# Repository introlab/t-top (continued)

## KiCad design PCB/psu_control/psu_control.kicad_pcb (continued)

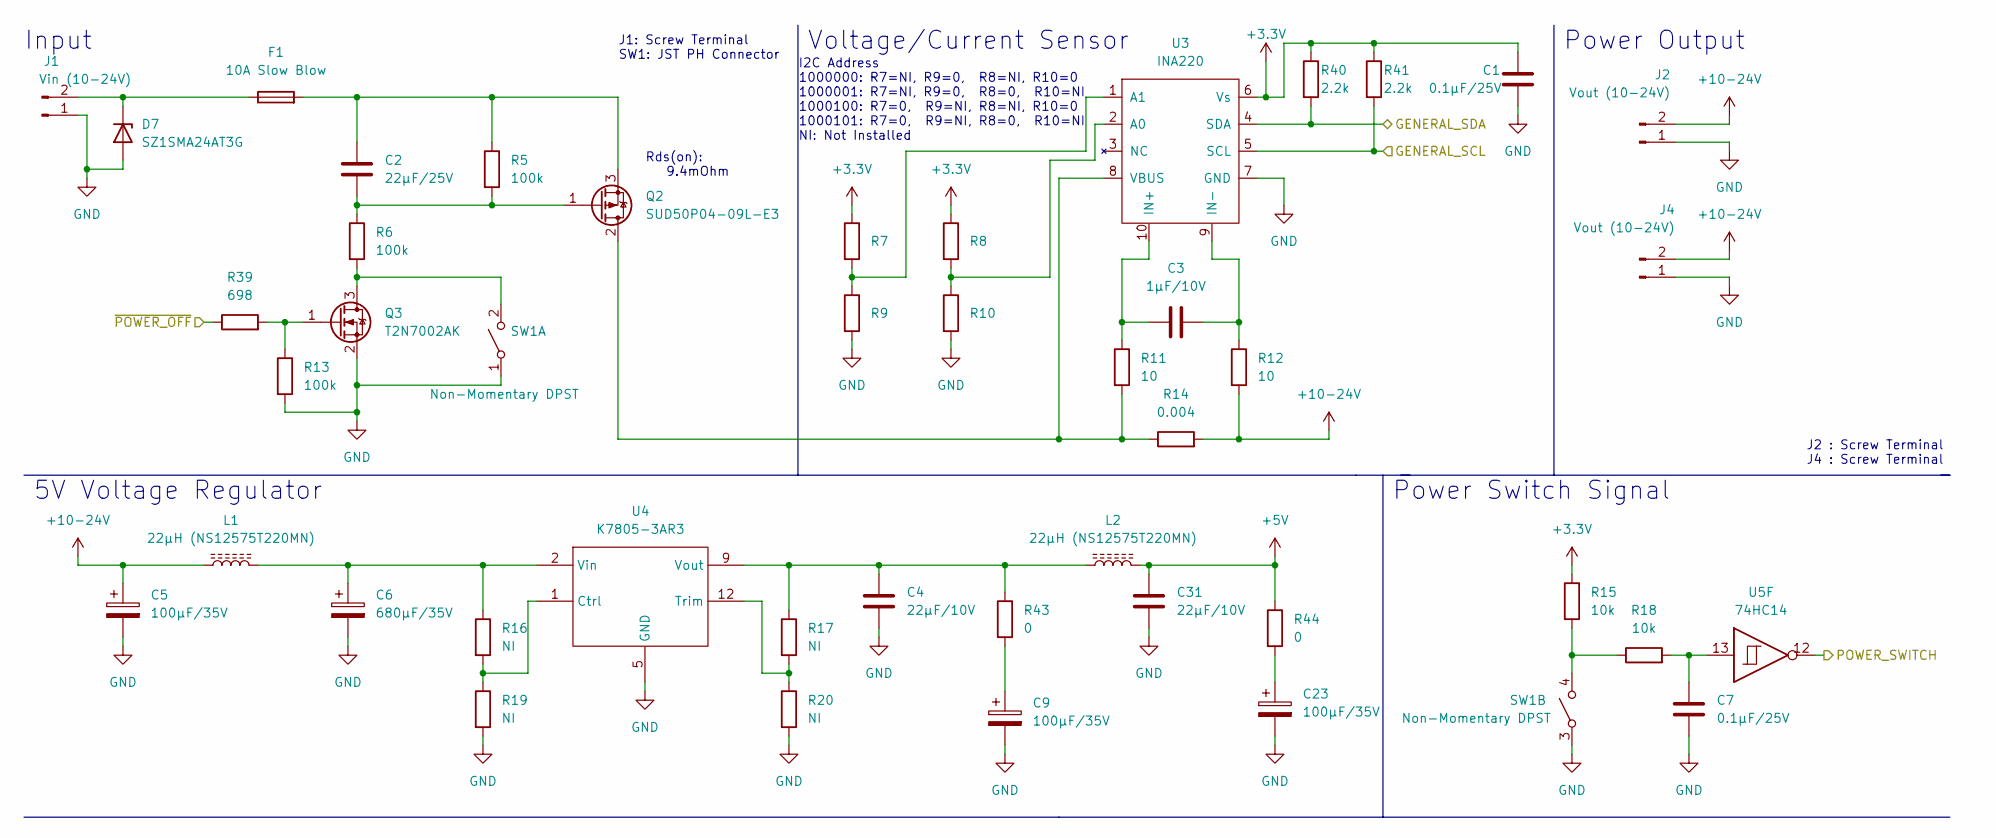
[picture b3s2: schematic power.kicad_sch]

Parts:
C1, C7: 0.1µF/25V; C_0805_2012Metric
C2: 22µF/25V; C_0805_2012Metric
C3: 1µF/10V; C_0805_2012Metric
C4, C31: 22μF/10V; C_0805_2012Metric
C5, C9, C23: 100µF/35V; CP_Radial_D6.3mm_P2.50mm
C6: 680µF/35V; CP_Radial_D10.0mm_P5.00mm
D7: SZ1SMA24AT3G; D_SMA
F1: 10A Slow Blow; M205_FUSE
J1: Vin (10-24V); OSTTA020161
J2, J4: Vout (10-24V); OSTTA020161
L1, L2: 22µH (NS12575T220MN); NS12575T220MN
Q2: SUD50P04-09L-E3; TO-252-2
Q3: T2N7002AK; SOT-23
R5, R6, R13: 100k; R_0805_2012Metric
R7, R8, R9, R10: 0; R_0805_2012Metric
R11, R12: 10; R_0805_2012Metric
R14: 0.004; R_1206_3216Metric
R15, R18: 10k; R_0805_2012Metric
R16, R17, R19, R20: NI; R_0805_2012Metric
R39: 698; R_0805_2012Metric
R40, R41: 2.2k; R_0805_2012Metric
R43, R44: 0; R_1206_3216Metric
SW1: Non-Momentary DPST; JST_PH_B4B-PH-K_1x04_P2.00mm_Vertical
U3: INA220; VSSOP-10_3x3mm_P0.5mm
U4: K7805-3AR3
U5: 74HC14; TSSOP-14_4.4x5mm_P0.65mm

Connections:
10-25V: C5.1, J2.2, J4.2, L1.1, R12.2, R14.2
+3.3V: C1.1, R7.1, R8.1, R15.1, R40.1, R41.1, U3.6 (Vs); also elsewhere on the board
+5V: C31.1, L2.2, R44.1; also elsewhere on the board
/GENERAL_SCL: R41.2, U3.5 (SCL); also elsewhere on the board
/GENERAL_SDA: R40.2, U3.4 (SDA); also elsewhere on the board
/POWER_SWITCH: U5.12; also elsewhere on the board
/~POWER_OFF: R39.1; also elsewhere on the board
GND: C1.2, C4.2, C5.2, C6.2, C7.2, C9.2, C23.2, C31.2, D7.2 (A), J1.1, J2.1, J4.1, Q3.2 (S), R9.2, R10.2, R13.2, R19.2, R20.2, SW1.1 (A), SW1.3 (A), U3.7 (GND), U4.5 (GND); also elsewhere on the board
unnamed: C2.1, F1.2, Q2.3 (S), R5.1
unnamed: C2.2, Q2.1 (G), R5.2, R6.1
unnamed: C3.1, R11.1, U3.10 (IN+)
unnamed: C3.2, R12.1, U3.9 (IN-)
unnamed: C4.1, L2.1, R17.1, R43.1, U4.9 (Vout)
unnamed: C6.1, L1.2, R16.1, U4.2 (Vin)
unnamed: C7.1, R18.2, U5.13
unnamed: C9.1, R43.2
unnamed: C23.1, R44.2
unnamed: D7.1 (K), F1.1, J1.2
unnamed: Q2.2 (D), R11.2, R14.1, U3.8 (VBUS)
unnamed: Q3.1 (G), R13.1, R39.2
unnamed: Q3.3 (D), R6.2, SW1.2 (B)
unnamed: R7.2, R9.1, U3.1 (A1)
unnamed: R8.2, R10.1, U3.2 (A0)
unnamed: R15.2, R18.1, SW1.4 (B)
unnamed: R16.2, R19.1, U4.1 (Ctrl)
unnamed: R17.2, R20.1, U4.12 (Trim)

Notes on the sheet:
Input
Power Output
Rds(on): 9.4mOhm
Power Switch Signal
J1: Screw Terminal SW1: JST PH Connector
5V Voltage Regulator
I2C Address 1000000: R7=NI, R9=0, R8=NI, R10=0 1000001: R7=NI, R9=0, R8=0, R10=NI 1000100: R7=0, R9=NI, R8=NI, R10=0 1000101: R7=0, R9=NI, R8=0, R10=NI NI: Not Installed
Voltage/Current Sensor
J2 : Screw Terminal J4 : Screw Terminal

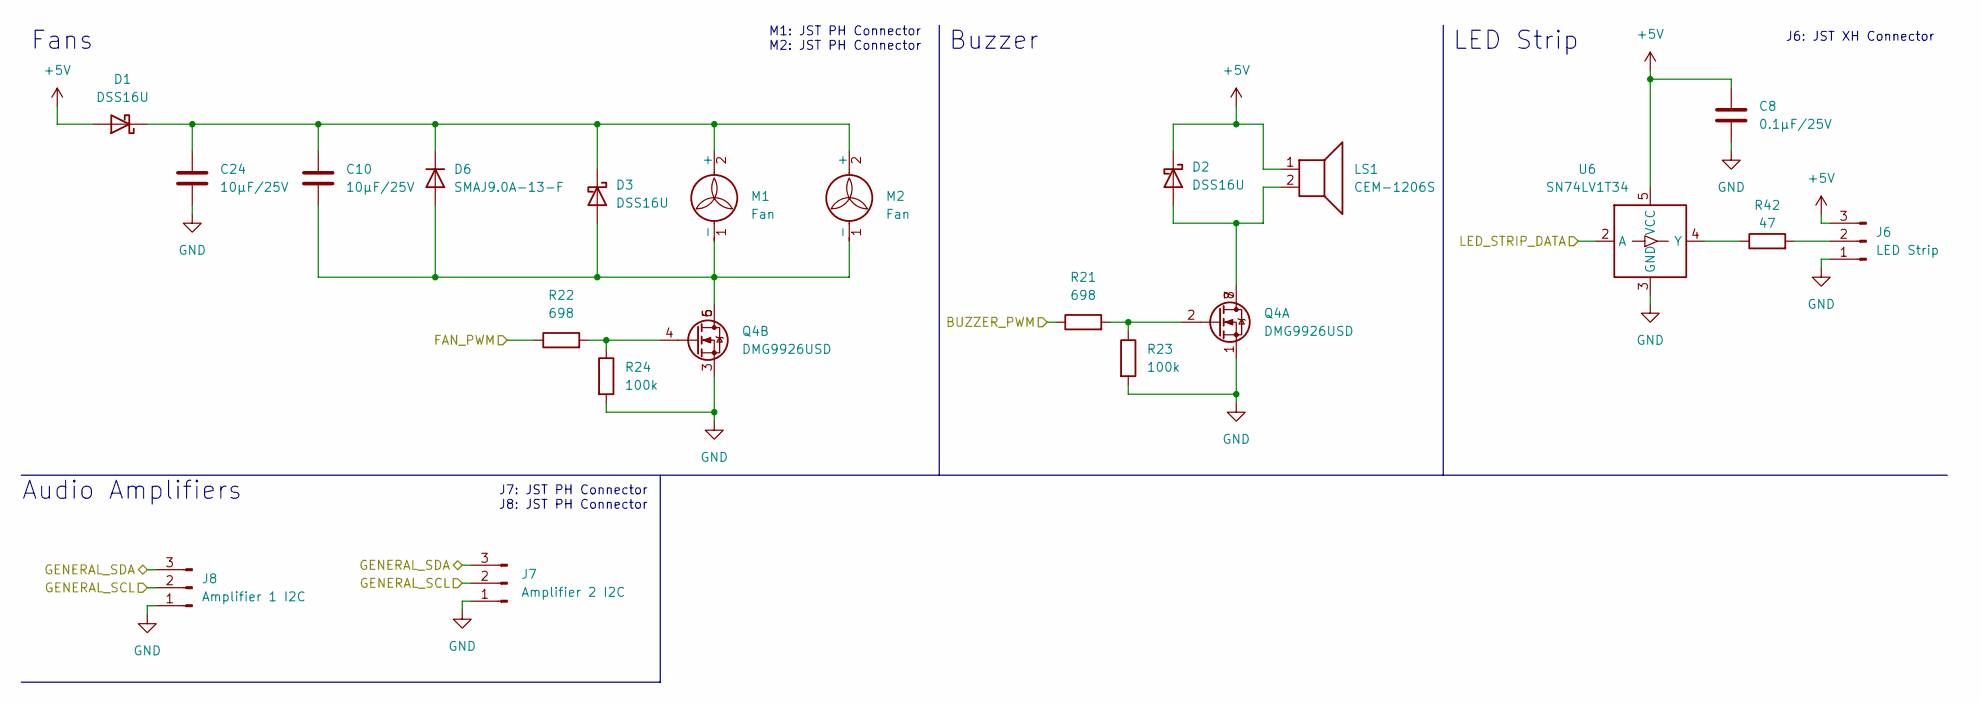
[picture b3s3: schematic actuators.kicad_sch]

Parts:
C8: 0.1µF/25V; C_0805_2012Metric
C10, C24: 10µF/25V; C_0805_2012Metric
D1, D2, D3: DSS16U; D_SOD-123F
D6: SMAJ9.0A-13-F; D_SMA
J6: LED Strip; JST_XH_B3B-XH-A_1x03_P2.50mm_Vertical
J7: Amplifier 2 I2C; JST_PH_B3B-PH-K_1x03_P2.00mm_Vertical
J8: Amplifier 1 I2C; JST_PH_B3B-PH-K_1x03_P2.00mm_Vertical
LS1: CEM-1206S; WT-1205
M1, M2: Fan; JST_PH_B2B-PH-K_1x02_P2.00mm_Vertical
Q4: DMG9926USD; SOIC-8_3.9x4.9mm_P1.27mm
R21, R22: 698; R_0805_2012Metric
R23, R24: 100k; R_0805_2012Metric
R42: 47; R_0805_2012Metric
U6: SN74LV1T34; SOT-23-5

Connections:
+5V: C8.1, D1.2 (A), D2.1 (K), J6.3, LS1.1, U6.5 (VCC); also elsewhere on the board
/Actuators/BUZZER_PWM: R21.1; also elsewhere on the board
/Actuators/FAN_PWM: R22.1; also elsewhere on the board
/Actuators/LED_STRIP_DATA: U6.2 (A); also elsewhere on the board
/GENERAL_SCL: J7.2, J8.2; also elsewhere on the board
/GENERAL_SDA: J7.3, J8.3; also elsewhere on the board
GND: C8.2, C24.2, J6.1, J7.1, J8.1, Q4.1 (S), Q4.3 (S), R23.2, R24.2, U6.3 (GND); also elsewhere on the board
unnamed: C10.1, C24.1, D1.1 (K), D3.1 (K), D6.1 (K), M1.2 (+), M2.2 (+)
unnamed: C10.2, D3.2 (A), D6.2 (A), M1.1 (-), M2.1 (-), Q4.5 (D), Q4.6 (D)
unnamed: D2.2 (A), LS1.2, Q4.7 (D), Q4.8 (D)
unnamed: J6.2, R42.2
unnamed: Q4.2 (G), R21.2, R23.1
unnamed: Q4.4 (G), R22.2, R24.1
unnamed: R42.1, U6.4 (Y)

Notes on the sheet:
Buzzer
Fans
J6: JST XH Connector
LED Strip
Audio Amplifiers
M1: JST PH Connector M2: JST PH Connector
J7: JST PH Connector J8: JST PH Connector

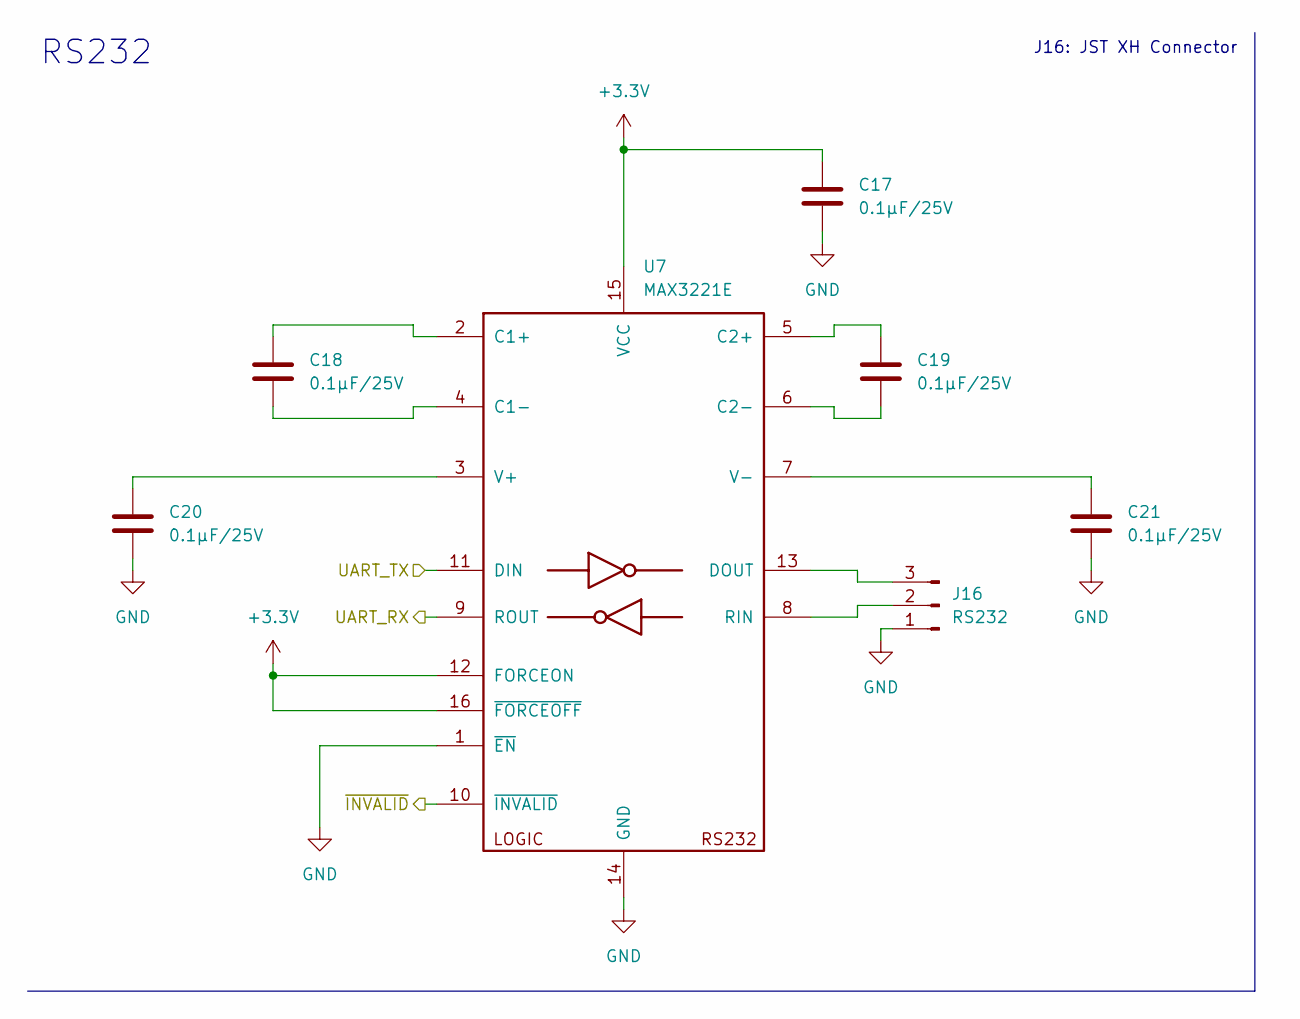
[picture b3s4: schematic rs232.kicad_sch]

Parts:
C17, C18, C19, C20, C21: 0.1µF/25V; C_0805_2012Metric
J16: RS232; JST_PH_B3B-PH-K_1x03_P2.00mm_Vertical
U7: MAX3221E; TSSOP-16_4.4x5mm_P0.65mm

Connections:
+3.3V: C17.1, U7.12 (FORCEON), U7.15 (VCC), U7.16 (~FORCEOFF); also elsewhere on the board
/RS232/UART_RX: U7.9 (ROUT); also elsewhere on the board
/RS232/UART_TX: U7.11 (DIN); also elsewhere on the board
/~RS232_INVALID: U7.10 (~INVALID); also elsewhere on the board
GND: C17.2, C20.2, C21.2, J16.1, U7.1 (~EN), U7.14 (GND); also elsewhere on the board
unnamed: C18.1, U7.2 (C1+)
unnamed: C18.2, U7.4 (C1-)
unnamed: C19.1, U7.5 (C2+)
unnamed: C19.2, U7.6 (C2-)
unnamed: C20.1, U7.3 (V+)
unnamed: C21.1, U7.7 (V-)
unnamed: J16.2, U7.8 (RIN)
unnamed: J16.3, U7.13 (DOUT)

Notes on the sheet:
J16: JST XH Connector
RS232

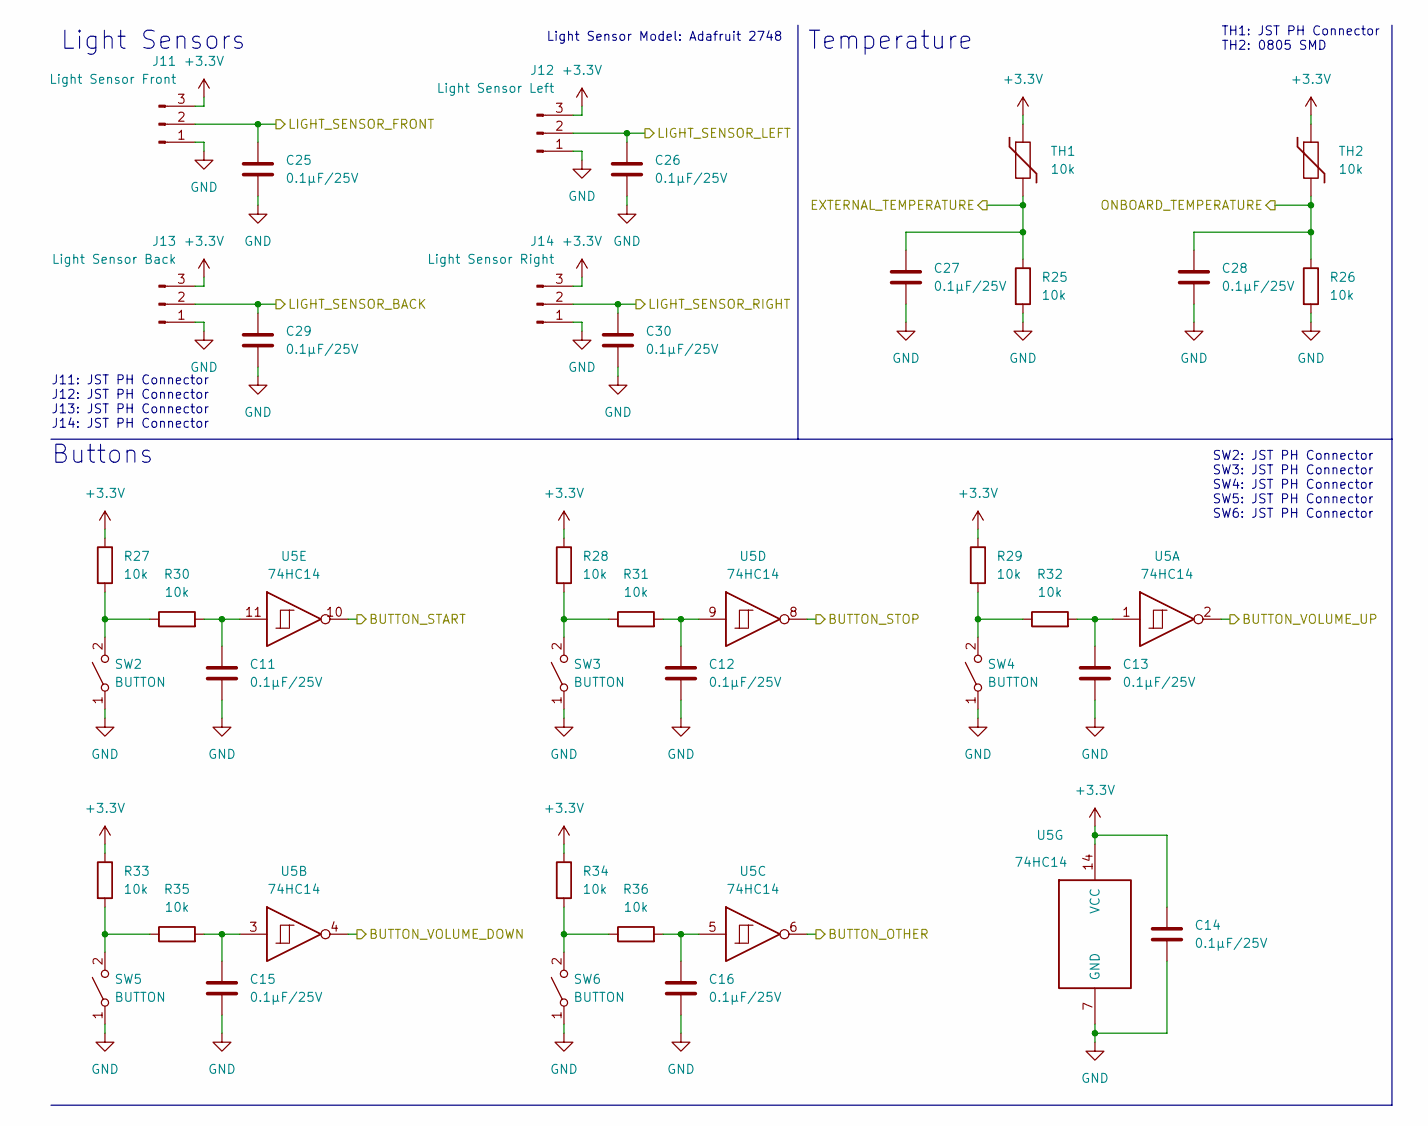
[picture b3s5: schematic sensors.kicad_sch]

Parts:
C11, C12, C13, C14, C15, C16, C25, C26, C27, C28, C29, C30: 0.1µF/25V; C_0805_2012Metric
J11: Light Sensor Front; JST_PH_B3B-PH-K_1x03_P2.00mm_Vertical
J12: Light Sensor Left; JST_PH_B3B-PH-K_1x03_P2.00mm_Vertical
J13: Light Sensor Back; JST_PH_B3B-PH-K_1x03_P2.00mm_Vertical
J14: Light Sensor Right; JST_PH_B3B-PH-K_1x03_P2.00mm_Vertical
R25, R26, R27, R28, R29, R30, R31, R32, R33, R34, R35, R36: 10k; R_0805_2012Metric
SW2, SW3, SW4, SW5, SW6: BUTTON; JST_PH_B2B-PH-K_1x02_P2.00mm_Vertical
TH1: 10k; JST_PH_B2B-PH-K_1x02_P2.00mm_Vertical
TH2: 10k; R_0805_2012Metric
U5: 74HC14; TSSOP-14_4.4x5mm_P0.65mm

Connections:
+3.3V: C14.1, J11.3, J12.3, J13.3, J14.3, R27.1, R28.1, R29.1, R33.1, R34.1, TH1.1, TH2.1, U5.14 (VCC); also elsewhere on the board
/BUTTON_OTHER: U5.6; also elsewhere on the board
/BUTTON_START: U5.10; also elsewhere on the board
/BUTTON_STOP: U5.8; also elsewhere on the board
/BUTTON_VOLUME_DOWN: U5.4; also elsewhere on the board
/BUTTON_VOLUME_UP: U5.2; also elsewhere on the board
/LIGHT_SENSOR_BACK: C29.1, J13.2; also elsewhere on the board
/LIGHT_SENSOR_RIGHT: C30.1, J14.2; also elsewhere on the board
/Sensors/EXTERNAL_TEMPERATURE: C27.1, R25.1, TH1.2; also elsewhere on the board
/Sensors/LIGHT_SENSOR_FRONT: C25.1, J11.2; also elsewhere on the board
/Sensors/LIGHT_SENSOR_LEFT: C26.1, J12.2; also elsewhere on the board
/Sensors/ONBOARD_TEMPERATURE: C28.1, R26.1, TH2.2; also elsewhere on the board
GND: C11.2, C12.2, C13.2, C14.2, C15.2, C16.2, C25.2, C26.2, C27.2, C28.2, C29.2, C30.2, J11.1, J12.1, J13.1, J14.1, R25.2, R26.2, SW2.1 (A), SW3.1 (A), SW4.1 (A), SW5.1 (A), SW6.1 (A), U5.7 (GND); also elsewhere on the board
unnamed: C11.1, R30.2, U5.11
unnamed: C12.1, R31.2, U5.9
unnamed: C13.1, R32.2, U5.1
unnamed: C15.1, R35.2, U5.3
unnamed: C16.1, R36.2, U5.5
unnamed: R27.2, R30.1, SW2.2 (B)
unnamed: R28.2, R31.1, SW3.2 (B)
unnamed: R29.2, R32.1, SW4.2 (B)
unnamed: R33.2, R35.1, SW5.2 (B)
unnamed: R34.2, R36.1, SW6.2 (B)

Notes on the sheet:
Buttons
SW2: JST PH Connector SW3: JST PH Connector SW4: JST PH Connector SW5: JST PH Connector SW6: JST PH Connector
TH1: JST PH Connector TH2: 0805 SMD
Light Sensors
Temperature
J11: JST PH Connector J12: JST PH Connector J13: JST PH Connector J14: JST PH Connector
Light Sensor Model: Adafruit 2748

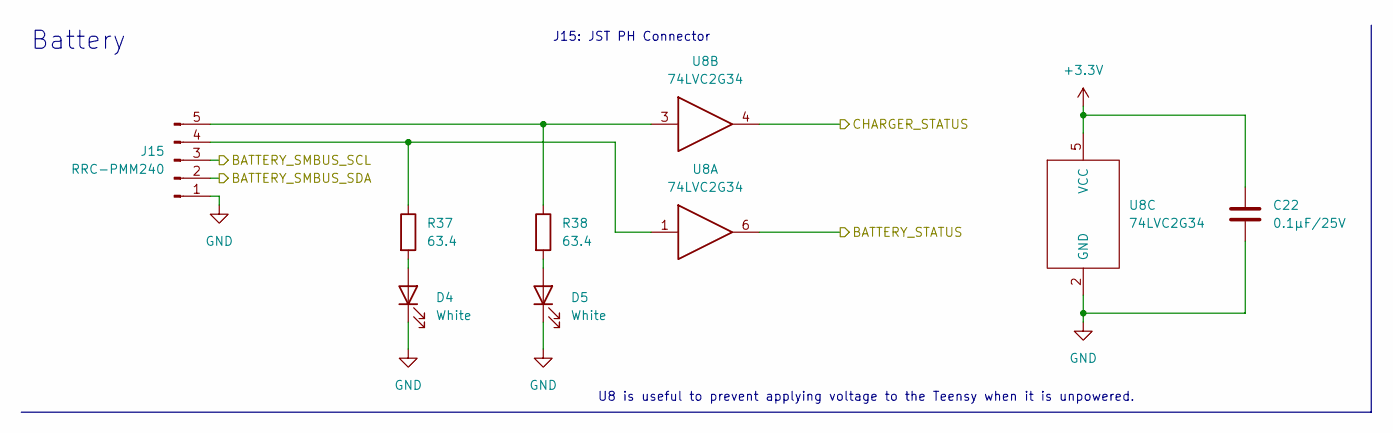
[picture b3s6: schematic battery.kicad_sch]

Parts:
C22: 0.1µF/25V; C_0805_2012Metric
D4, D5: White; JST_PH_B2B-PH-K_1x02_P2.00mm_Vertical
J15: RRC-PMM240; JST_PH_B5B-PH-K_1x05_P2.00mm_Vertical
R37, R38: 63.4; R_0805_2012Metric
U8: 74LVC2G34; TSOP-6_1.65x3.05mm_P0.95mm

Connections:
+3.3V: C22.1, U8.5 (VCC); also elsewhere on the board
/Battery/BATTERY_SMBUS_SCL: J15.3; also elsewhere on the board
/Battery/BATTERY_SMBUS_SDA: J15.2; also elsewhere on the board
/Battery/BATTERY_STATUS: U8.6; also elsewhere on the board
/Battery/CHARGER_STATUS: U8.4; also elsewhere on the board
GND: C22.2, D4.1 (K), D5.1 (K), J15.1, U8.2 (GND); also elsewhere on the board
unnamed: D4.2 (A), R37.2
unnamed: D5.2 (A), R38.2
unnamed: J15.4, R37.1, U8.1
unnamed: J15.5, R38.1, U8.3

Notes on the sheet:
Battery
U8 is useful to prevent applying voltage to the Teensy when it is unpowered.
J15: JST PH Connector

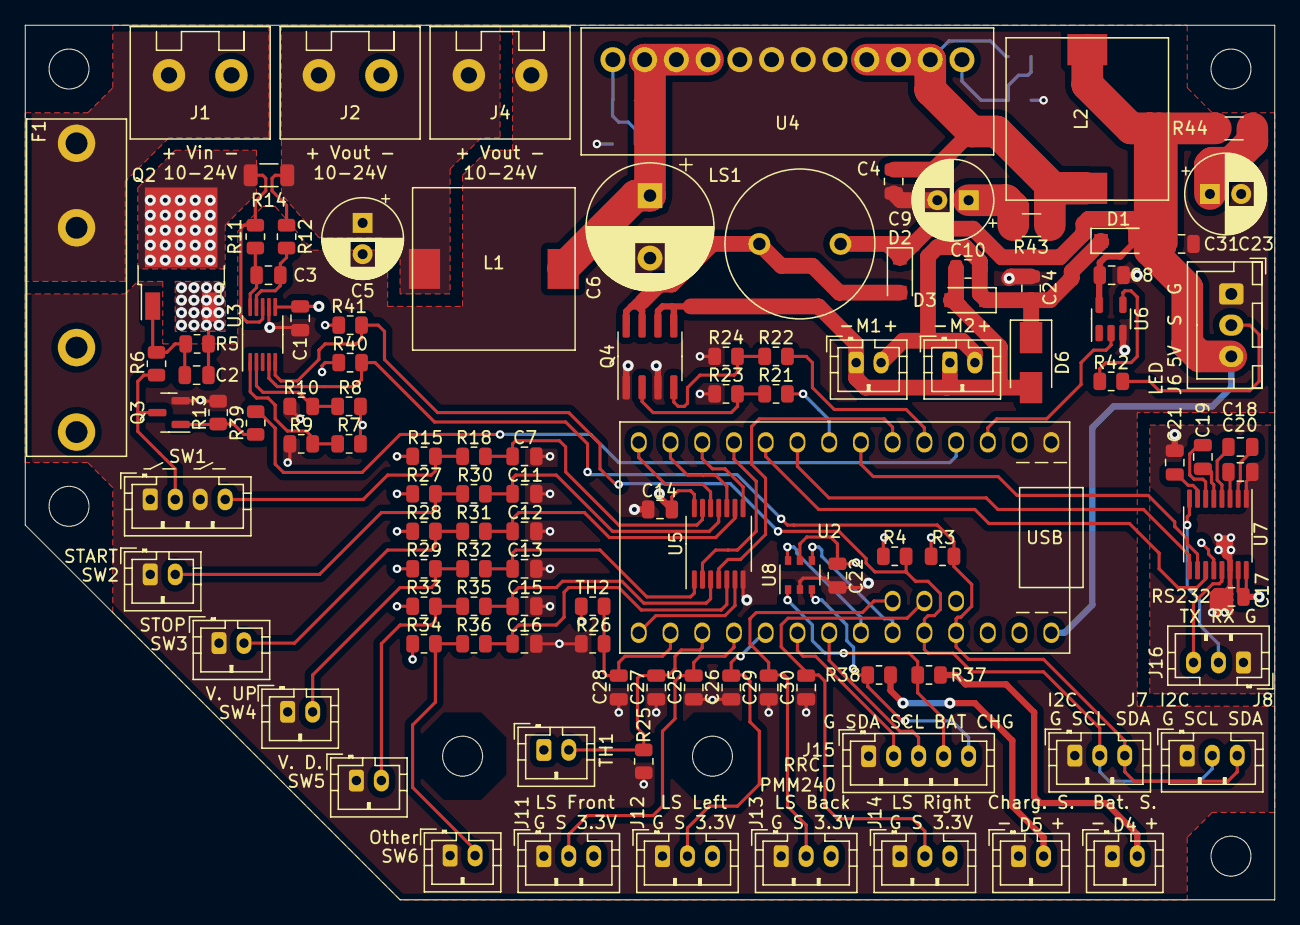
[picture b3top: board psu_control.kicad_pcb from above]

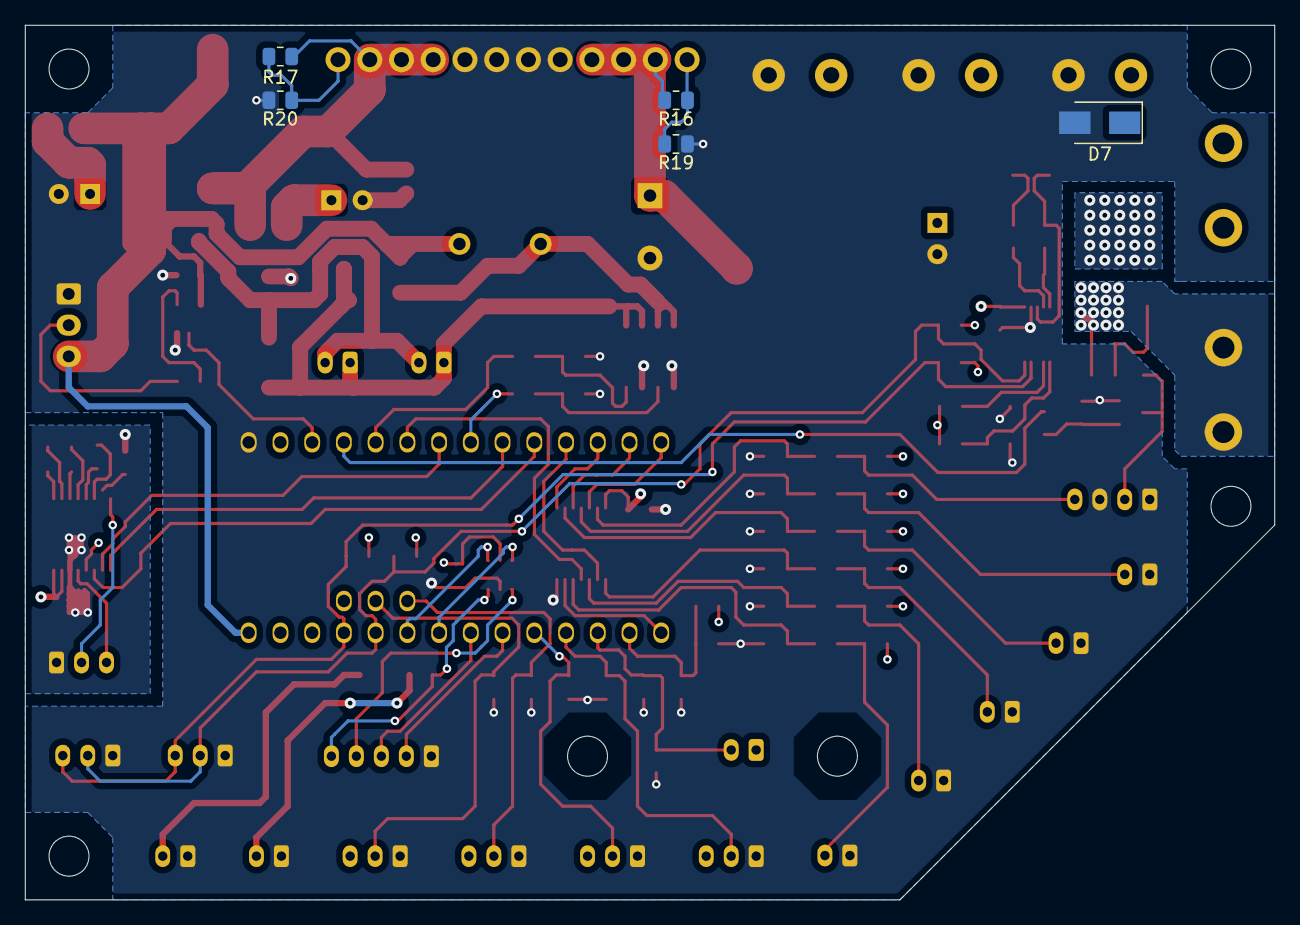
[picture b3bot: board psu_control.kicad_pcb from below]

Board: 4 copper layers, 100.0 x 70.0 mm, 116 parts (5 on the bottom side), 76 nets.

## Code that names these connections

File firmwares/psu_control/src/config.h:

#ifndef PSU_CONTROL_CONFIG_H
#define PSU_CONTROL_CONFIG_H

#include <cstdint>
#include <cstddef>

// Firmware configuration
#define FIRMWARE_MODE_SETUP_BATTERY_CHARGER 1
#define FIRMWARE_MODE_NORMAL                2
#define FIRMWARE_MODE_PCB_TEST              3
#define FIRMWARE_MODE_COMMUNICATION_TEST    4
#define FIRMWARE_MODE                       FIRMWARE_MODE_NORMAL

// Device configuration
#define DEBUG_SERIAL Serial
constexpr long DEBUG_SERIAL_BAUD_RATE = 250000;

constexpr uint32_t WIRE_CLOCK = 100000;

constexpr uint32_t PWM_RESOLUTION = 12;
constexpr float PWM_MAX_VALUE = 4095.f;

constexpr uint32_t ADC_RESOLUTION = 12;
constexpr float ADC_MAX_VALUE = 4095.f;

constexpr uint8_t POWER_OFF_PIN = 2;
constexpr uint8_t POWER_SWITCH_PIN = 12;
constexpr uint32_t SHUTDOWN_REQUEST_TIMEOUT_MS = 120000;
constexpr float SHUTDOWN_COMPLETED_FOR_COMPUTER_AND_DYNAMIXELS_POWER_THRESHOLD_W = 7.5f;

#define BATTERY_WIRE Wire
constexpr uint8_t BATTERY_STATUS_PIN = 20;
constexpr uint8_t CHARGER_STATUS_PIN = 21;
constexpr float BATTERY_CHARGER_CHARGE_CURRENT_LIMIT = 1.f;
constexpr float BATTERY_CHARGER_INPUT_CURRENT_LIMIT = 9.47f;

constexpr uint8_t LED_STRIP_PIN = 1;
constexpr size_t STATE_OF_CHARGE_LED_COUNT = 5;
constexpr size_t VOLUME_LED_COUNT = 5;
constexpr size_t BASE_LED_COUNT = 28;
constexpr size_t LED_COUNT = STATE_OF_CHARGE_LED_COUNT + VOLUME_LED_COUNT + BASE_LED_COUNT;
constexpr uint8_t LED_STRIP_MINIMUM_BRIGHTNESS = 64;
constexpr uint8_t LED_STRIP_MAXIMUM_BRIGHTNESS = 128;

constexpr uint8_t FAN_PIN = 3;
constexpr float FAN_PWM_FREQUENCY = 46875;
constexpr float FAN_HYSTERESIS = 1;
constexpr float FAN_TEMPERATURE_STEP_1 = 40;
constexpr float FAN_TEMPERATURE_STEP_2 = 60;

constexpr uint8_t BUZZER_PIN = 6;
constexpr float BUZZER_PWM_FREQUENCY = 2400;
constexpr uint32_t BUZZER_ON_OFF_INTERVAL_US = 1000000;
constexpr float BUZZER_STATE_OF_CHARGE_LIMIT = 5;

#define AUDIO_POWER_AMPLIFIER_WIRE Wire1
constexpr size_t AUDIO_POWER_AMPLIFIER_COUNT = 2;
constexpr uint8_t AUDIO_POWER_AMPLIFIER_I2C_ADDRESSES[AUDIO_POWER_AMPLIFIER_COUNT] = {0x4a, 0x4b};
constexpr uint8_t AUDIO_POWER_AMPLIFIER_DEFAULT_VOLUME = 24;
constexpr uint8_t AUDIO_POWER_AMPLIFIER_BATTERY_MAXIMUM_VOLUME = 45;
constexpr uint8_t AUDIO_POWER_AMPLIFIER_MAXIMUM_VOLUME = 63;

#define CURRENT_VOLTAGE_SENSOR_WIRE Wire1
constexpr uint8_t CURRENT_VOLTAGE_SENSOR_ADDRESS = 0x40;
constexpr float CURRENT_VOLTAGE_SENSOR_SHUNT_RESISTOR = 0.004f;
constexpr uint8_t CURRENT_VOLTAGE_SENSOR_MAX_CURRENT = 10;

constexpr uint8_t ONBOARD_TEMPERATURE_PIN = 14;
constexpr float ONBOARD_TEMPERATURE_NTC_R = 10000;  // @ 25°C
constexpr float ONBOARD_TEMPERATURE_NTC_BETA = 3940;
constexpr float ONBOARD_TEMPERATURE_R = 10000;
constexpr uint8_t EXTERNAL_TEMPERATURE_PIN = 15;
constexpr float EXTERNAL_TEMPERATURE_NTC_R = 10000;  // @ 25°C
constexpr float EXTERNAL_TEMPERATURE_NTC_BETA = 3936;
constexpr float EXTERNAL_TEMPERATURE_R = 10000;

constexpr uint8_t FRONT_LIGHT_SENSOR_PIN = 16;
constexpr uint8_t BACK_LIGHT_SENSOR_PIN = 25;
constexpr uint8_t LEFT_LIGHT_SENSOR_PIN = 17;
constexpr uint8_t RIGHT_LIGHT_SENSOR_PIN = 24;
constexpr float LIGHT_SENSOR_MINIMUM_VALUE = ADC_MAX_VALUE * 0.0f;
constexpr float LIGHT_SENSOR_MAXIMUM_VALUE = ADC_MAX_VALUE * 0.03f;

constexpr uint8_t START_BUTTON_PIN = 11;
constexpr uint8_t STOP_BUTTON_PIN = 10;
constexpr uint8_t VOLUME_UP_BUTTON_PIN = 9;
constexpr uint8_t VOLUME_DOWN_BUTTON_PIN = 4;
constexpr uint32_t VOLUME_BUTTON_INTERVAL_MS = 250;

// Communication configuration
#define COMMUNICATION_SERIAL Serial3
constexpr uint8_t COMMUNICATION_RS232_INVALID = 5;
constexpr long COMMUNICATION_SERIAL_BAUD_RATE = 250000;
constexpr uint32_t COMMUNICATION_ACKNOWLEDGMENT_TIMEOUT_MS = 100;
constexpr uint32_t COMMUNICATION_MAXIMUM_TRIAL_COUNT = 5;

// Timing configuration
constexpr uint32_t ERROR_DELAY_MS = 1000;
constexpr uint32_t STATUS_TICKER_INTERVAL_MS = 250;
constexpr uint32_t BUTTON_TICKER_INTERVAL_MS = 100;
constexpr uint32_t SHUTDOWN_PENDING_DELAY_MS = 1000;

#endif

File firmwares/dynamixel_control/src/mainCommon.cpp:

#include "mainCommon.h"

Icm40627 imu(Wire, IMU_INT1_PIN, IMU_INT2_PIN, IMU_ADDRESS);
Dynamixel2Arduino dynamixel(DYNAMIXEL_SERIAL, DYNAMIXEL_DIR_PIN);

void setupDebugSerial()
{
    DEBUG_SERIAL.begin(DEBUG_SERIAL_BAUD_RATE);
}

void setupWire()
{
    DEBUG_SERIAL.println("Setup Wire - Start");
    Wire.setClock(WIRE_CLOCK);
    Wire.begin();
    DEBUG_SERIAL.println("Setup Wire - End");
}

void setupImu()
{
    DEBUG_SERIAL.println("Setup Imu - Start");
    if (!imu.begin(IMU_ACCELEROMETER_RANGE, IMU_GYROSCOPE_RANGE, IMU_ODR, IMU_ANTI_ALIAS_FILTER_BANDWIDTH))
    {
        CRITICAL_ERROR("Setup Imu - failure");
    }
    DEBUG_SERIAL.println("Setup Imu - End");
}

void setupImu(void (*dataReadyInterrupt)())
{
    DEBUG_SERIAL.println("Setup Imu - Start");
    if (!imu.begin(IMU_ACCELEROMETER_RANGE, IMU_GYROSCOPE_RANGE, IMU_ODR, IMU_ANTI_ALIAS_FILTER_BANDWIDTH, dataReadyInterrupt))
    {
        CRITICAL_ERROR("Setup Imu - failure");
    }
    DEBUG_SERIAL.println("Setup Imu - End");
}

void setupDynamixel()
{
    DEBUG_SERIAL.println("Setup Dynamixel - Start");

    pinMode(DYNAMIXEL_ENABLE_PIN, OUTPUT);
    digitalWrite(DYNAMIXEL_ENABLE_PIN, true);

    dynamixel.begin(DYNAMIXEL_BAUD_RATE);
    delay(SETUP_DYNAMIXEL_DELAY_MS);

    DEBUG_SERIAL.println("Setup Dynamixel - End");
}

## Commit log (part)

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2023-11-18 Update tab_leds.png in control_panel.
2023-11-20 Improve robot name detection.
2023-11-20 Fix createRobotNameDetectorWithLedStatusDesireStrategy
2023-11-20 Add prebuffering to whisper_speech_to_text_node.py.
2023-11-20 Fix whisper_speech_to_text_node activation. Fix robot_name_detector status disabling.
2023-11-20 Reset the fast sound rms filter to prevent triggering at the activation of the node.
2023-11-20 Fix robot_name_detector.
2023-11-20 Fix connect4.launch
2023-11-20 Fix robot_name_detector inference_type.
2023-11-22 Added slow_origin_head and thinking gestures
2023-11-26 Add the node to analyze the performance of YOLO models.
2023-11-27 Update nvpmodel.
2023-12-04 Update SHUTDOWN_COMPLETED_FOR_COMPUTER_AND_DYNAMIXELS_POWER_THRESHOLD_W.
2023-12-05 Add a watchdog node for the wide-angle camera.
2023-12-05 Add arbitration for the head pose and torso orientation.
2023-12-06 Fix sound_following_node.py
2023-12-06 Fix face_following_nodes
2023-12-06 Fix too_near_reaction.launch
2023-12-06 Reset the offset of too_near_reaction on disabling.
2023-12-06 Add the video analysis object in the pose classification message.
2023-12-06 Rename too near reaction to too close reaction.
2023-12-07 Complete yolo_performance.
2023-12-10 Ubc demo (#83)
    * Disable semantic segmentation.
    * Add pose classification.
    * Remove prints.
    * Increased timeout to 20 sec and use google cloud url. Use wide angle camera for pose classification.
    * Decrease presence threshold
    * Cache size is now 1000
2023-12-10 Use a uuid for the image filename.
2023-12-12 5s watchdog
2023-12-19 Add the LED animation when a participant win a game.
2023-12-19 Update opentera-webrtc
2024-01-10 Use web socket to get the game feedback.
2024-01-10 Yolo detection results (#84)
    * Add the node to analyze the performance of YOLO models.
    * Complete yolo_performance.
    * Add the scripts to the CMakeLists.txt
    * Use a uuid for the image filename.
2024-01-11 Add face orientation replication draft.
2024-01-11 Add topic args to the data channel launch file.
2024-01-11 Add webrtc face orientation.
2024-01-15 Update HBBA Lite
2024-01-15 Update hbba_lite
2024-01-16 Update opentera-webrtc-ros.
2024-01-16 Adjust face orientation replication parameters.
2024-01-17 Add head_roll_image_rotation_node.py draft.
2024-01-17 Fix rotation direction.
2024-01-19 Set the stamp and seq of the output msg.
2024-01-26 Update papers in README.md.
2024-02-20 fix delay before talk done
2024-02-20 Fix talk done delay. Fix when cache size is zero. Delete cache files when needed.
2024-03-19 Add yolo model arguments to the bringup.launch. Fix the dnn_utils readme. Add class AP for multiclass audio classification.
2024-03-20 Fix bringup.launch
2024-04-03 Removed ROS print
2024-04-05 Added stats to transcript
2024-04-05 Fixing google processing time and sample count
2024-04-08 Try calling API for stats
2024-04-08 GitHub stats (#91)
    * Try calling API for stats
    * Try calling API for stats
    * Try calling API for stats
    * Try calling API for stats
    * Try calling API for stats
    * Update scheduled-stats.yml
2024-04-09 Update README.md papers
2024-04-12 Adding processing time to video analysis.
2024-04-12 Adding stats to talk node
2024-04-15 Moved stats into a function
2024-04-15 Fix launch files that use video_analyzer.launch directly.
2024-04-15 Use the GPU for the face cropper.
2024-04-15 Speech stats (#92)
    * Added stats to transcript
    * Fixing google processing time and sample count
    * Updated time, looks more than the response time than the processing time since the last final sentence
    * Adding processing time to analysis message
    * Adding processing time to video analysis.
    * Adding stats to talk node
2024-04-15 Fix launch files (#93)
    * Fix launch files that use video_analyzer.launch directly.
    * Use the best network for face cropping.
    * Use the GPU for the face cropper.
    * Updated opentera-webrtc-ros
    ---------
2024-04-29 Make thresholds global for video_analyzer
2024-04-29 Updated hbba_lite to fix semaphore implementation. Now using C++ 17
2024-04-29 Adding whisper model
2024-04-29 Build the user interface at build time.
2024-04-29 Reduce the sleep duration
2024-05-03 Add a way to evaluate the descriptor yolo v7 descriptor.
2024-05-08 Adding delays when launching nodes.
2024-05-08 Fix delays (#98)
    * Build the user interface at build time.
    * Reduce the sleep duration
    * Adding delays when launching nodes.
    * add more delays
    ---------
2024-05-09 Working on ARM
2024-05-09 Fix version for ARM
2024-05-13 Update descriptor yolo v7 weights.
2024-05-14 Realsense respawn (#103)
    * Build the user interface at build time.
    * Reduce the sleep duration
    * Updated launch file to set respawn to true for realsense
    ---------
2024-05-16 Added missing delays and thresholds
2024-05-16 Building ros2 realsense node with cuda, WIP
2024-05-17 launching realsense and bridge
2024-05-28 Evaluate descriptor yolo (#102)
    * Add a way to evaluate the descriptor yolo v7 descriptor.
    * Update descriptor yolo v7 weights.
2024-05-28 Add ros2 submodules.
2024-05-28 Ignore system projects.
2024-05-28 Add dnn_utils
2024-05-28 Add daemon_ros_client
2024-05-28 Add video_analyzer
2024-05-28 Add robot_name_detector.
2024-05-28 Add speech_to_text
2024-05-30 Add t_top without launch. Refatoring.
2024-05-30 Add dance.
2024-05-30 Add gesture.
2024-05-30 Add led_emotions
2024-05-30 Add piper_ros
2024-05-30 Add sound_player
2024-05-30 Add talk
2024-05-30 Add t-top_hbba_lite
2024-05-31 Add ego_noise_reduction
2024-06-01 Fix DaemonApp.cpp. Add person_identification.
2024-06-01 Add sound_object_person_following
2024-06-01 Add yolo_performance.
2024-06-01 Add control_panel
2024-06-01 Add smart_speaker
2024-06-03 Update .gitmodules
    use https instead of git.
2024-06-03 Almost compiling RTAB-Map
2024-06-03 Changed to humble ros2 distribution
2024-06-03 Complete video_recorder_node.py
2024-06-04 Add watchdog.
2024-06-04 Format
2024-06-05 Building with rtabmap
2024-06-05 Building ok
2024-06-05 Move behavior msg to behavior_msg.
2024-06-06 updated docker build
2024-06-06 Fix for audio_utils_msg and humble.
2024-06-06 add install script
2024-06-06 Update test_video_analyzer_3d_node.launch.xml.
2024-06-07 ongoing fix for launch files
2024-06-10 set number of proc properly
2024-06-10 Fixed ROS_ROOT prefix
2024-06-10 fixed xml
2024-06-10 Fixed XML launch files
2024-06-10 fixed format parameter
2024-06-18 Fix rclpy.shutdown().
2024-06-18 Fixed shutdown, need to fix camera calibration, talk
2024-06-19 Launching works. Fixed shutdown. Fix deadlocks.
2024-06-20 Fix SQLiteCpp
2024-06-20 Fix ego_noise_reduction. Fix video_analyzer vizualisation nodes. Fix yolo_performance.
2024-06-20 Fix home_logger.
2024-06-20 Add first draft of jetson_configuration.sh for ROS2.
2024-06-21 Better dependencies export for hbba_lite and t_top_hbba_lite, simplifies CMake in demos
2024-06-21 Migrate teleoperation behavior
2024-06-22 Fix build for CMake 3.22.1
2024-06-28 Fixed compilation with hbba and odas_ros
2024-06-28 Updated odas_ros
2024-07-03 Fix delays and ifs
2024-07-03 updated gui
2024-07-03 Fix WiFi network name in robot_status
2024-07-05 Connect4 cpp migration
2024-07-05 Test face orientation working, fix launch files
2024-07-05 Added opentera-webrtc-ros
2024-07-05 Add missing ros2 packages.
2024-07-06 Update odas_ros and hbba_lite.
2024-07-12 Fix roll_angle_rad initialization
2024-07-12 Added build flags, Release
2024-07-12 Add information about ROS_DOMAIN_ID
2024-07-17 Improve audio_analyzer_node.py descriptors.
2024-07-26 Set all audio queue size to 1.
2024-11-05 Fix jetson_configuration.sh
2024-11-05 Update 13_CALIBRATION.md
    Create calib path.
2024-11-05 Update ros2_humble_install.sh
    Fix build.
2025-01-09 Fix warnings
2025-01-13 Fix warnings in submodules
2025-01-22 Fix duplicate tf, npm no longer clear terminal
2025-01-22 Fix install script for t-top v4 for ROS2, jetson orin and jetpack 5.1.4
2025-02-17 Adding ChatDesire and ChatStrategy, WIP.
2025-02-17 Demo enabling ChatStrategy working. WIP.
2025-02-19 Working chat with ollama
2025-02-20 Fix warnings (#108)
    * Fix warnings
    * Fix warnings in submodules
    * Hide npm warnings if the user_interface build is a success
    * Fix duplicate tf, npm no longer clear terminal
    * Fix install script for t-top v4 for ROS2, jetson orin and jetpack 5.1.4
    * Update submodules
2025-02-26 Updated to ros2 branch
2025-02-28 Fix websocket url in diner game, code improvements
2025-03-03 Working simple function calls
2025-03-06 Handle second next_configuration and stop event
2025-03-13 Update README.md
    Fix mailto
2025-03-13 Add files via upload
    Removed alpha.
2025-03-31 Starting work on getting started documentation
2025-04-01 Added debug configuration
2025-04-01 Starting separation into configuration files
2025-04-01 Added diner scenario handling (#109)
    * Added diner scenario handling
    * Fix websocket url in diner game, code improvements
    * Fix websocket url in diner game, code improvements
    * Fix websocket url in diner game, code improvements
    * Handle second next_configuration and stop event
2025-04-10 Getting started doc (#111)
    * Starting work on getting started documentation
    * Added control panel launch
    * Added debug configuration
    * Fixed documentation
2025-04-15 Calling external services, WIP
2025-04-16 Callbacks blocking after calling service, why ?
2025-04-16 Trying another thread, same result, not receiving subscriber message
2025-04-23 Working version to raise or lower volume
2025-04-23 Cleanup
2025-04-25 Updated documentation
2025-04-30 Fix path to file to source in integrated terminal profile
2025-04-30 Address remaining pull request comments.
2025-04-30 Add robot Wifi IP address to system tray to make it easier to check (#114)
2025-04-30 Fix path to file to source in integrated terminal profile (#113)
2025-05-01 Fix openai api for openai > 1.0.0
2025-05-09 Fix Chatbot synchronization
2025-05-12 Added new filter for chat behavior translation subscriber, republishing transcript from strategy.
2025-05-13 fixed documentation and filter activation order.
2025-05-13 fixed documentation.
2025-05-14 add perception conversation revive
2025-05-16 add weather request api
2025-05-21 add weather function call
2025-05-30 change meteo node name in launch
2025-06-03 PR modifications
2025-06-04 Added weather data for current weather
2025-06-04 Removed time from msg and added classes.json
2025-06-06 function call tools librairy
2025-06-10 Add get_activity function
2025-06-10 install and export chattools librairy
2025-06-12 Add save history capabilities + PR adjustment
2025-06-12 adjust launch file + save condition
2025-06-12 modify path
2025-06-13 meteo days index update
2025-06-16 remove chat
2025-06-18 Chat_node history save update msg + path
2025-06-27 split process response
2025-07-01 statemachine commit 1
2025-07-14 clean from stateMachine
2025-07-14 remove chat revive logic
2025-07-14 Remove Revive from ContextInput
2025-07-15 clean current object from strategy
2025-07-17 Remove old weather api
2025-07-23 tool_call adjustment
2025-07-25 update hint and plural
2025-07-25 plural fix
2025-09-05 Update Chatbot (#121)
    * skeleton
    * Adding ChatDesire and ChatStrategy, WIP.
    * Base chatbot demo
    * Demo enabling ChatStrategy working. WIP.
    * Working chat with ollama
    * Working chatbot
2025-10-06 fix save path to avoid problems with user names, make sure file is saved with proper path
2026-01-11 WIP: add compatibility with ROS2 version of TOPO
2026-02-03 Deprecated parameters for gpt-5-mini (#125)
2026-05-21 Added text based end of utterance detection node to reduce t-top interruptions
2026-06-26 Added docstrings in stt node
